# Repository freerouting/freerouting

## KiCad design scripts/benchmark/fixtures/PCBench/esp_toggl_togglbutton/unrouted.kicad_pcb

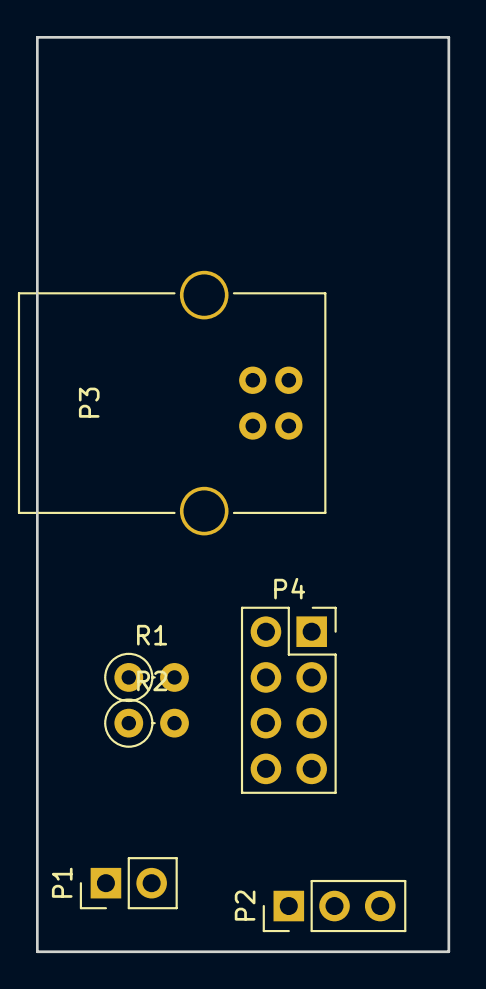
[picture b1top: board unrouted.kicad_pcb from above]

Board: 2 copper layers, 22.9 x 50.8 mm, 7 parts (1 on the bottom side), 7 nets, no tracks yet.

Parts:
P1: Button; Pin_Header_Straight_1x02_Pitch2.54mm
P2: WS2812B; Pin_Header_Straight_1x03_Pitch2.54mm
P3: USB_B
P4: CONN_02X04; Socket_Strip_Straight_2x04_Pitch2.54mm
R1, R2: 10k; R_Axial_DIN0207_L6.3mm_D2.5mm_P2.54mm_Vertical
U1: NCP1117ST33T3G; SOT-223

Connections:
+5V: P2.3, P3.1, U1.3
GND: P1.1, P2.1, P3.4, P3.5, P4.1, U1.1
unnamed: P1.2, P4.5
unnamed: P2.2, P4.3
unnamed: P4.4, R1.2
unnamed: P4.6, R2.2
unnamed: P4.8, R1.1, R2.1, U1.2

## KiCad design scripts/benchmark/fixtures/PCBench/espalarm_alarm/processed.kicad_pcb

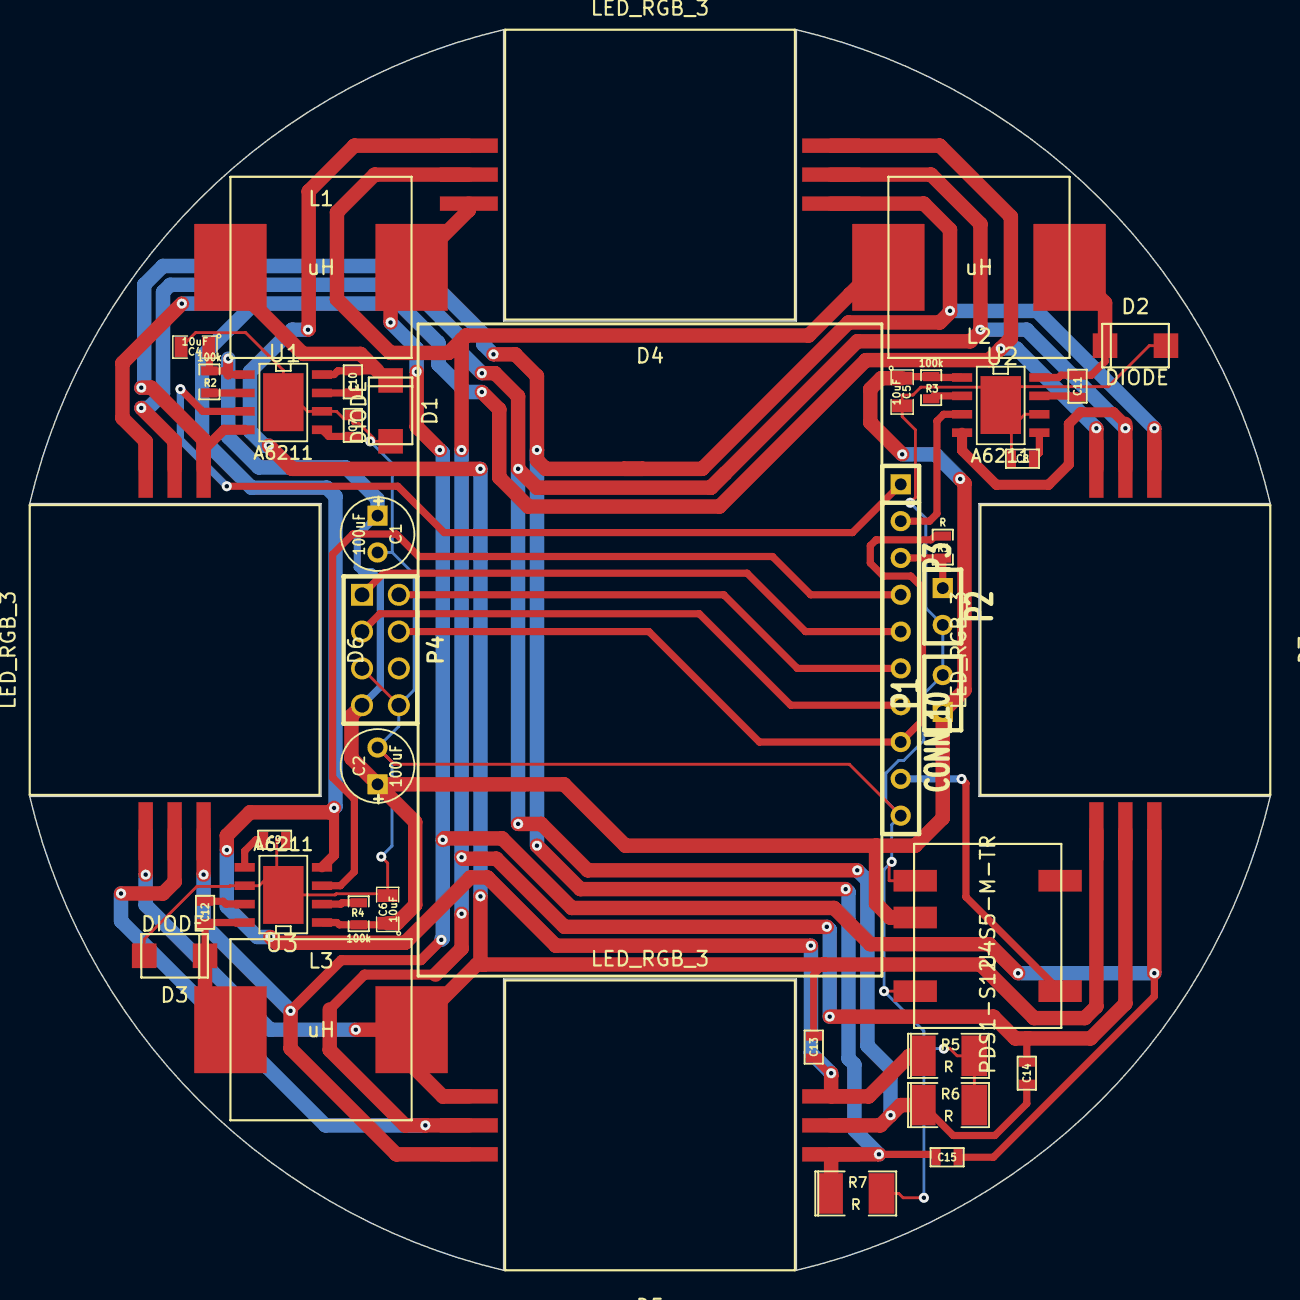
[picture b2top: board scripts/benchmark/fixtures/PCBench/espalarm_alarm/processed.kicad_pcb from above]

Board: 2 copper layers, 85.6 x 85.6 mm, 39 parts (0 on the bottom side), 29 nets.

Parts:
C1, C2: 100uF; C1V5
C4, C5, C6: 10uF; SM0805
C7, C8, C9, C10, C11, C12: 100nF; SM0603
C13, C14, C15: 1uF; SM0603
D1, D2, D3: DIODE; DIODE_SMA
D4, D5, D6, D7: LED_RGB_3; RGB_LED_10W
L1, L2, L3: uH; IND_12.5x12.5mm
P1, P2: CONN_2; SIL-2
P3: CONN_10; SIL-10
P4: CONN_8; pin_array_4x2
R1: R; SM0603_Resistor
R2, R3, R4: 100k; SM0603_Resistor
R5, R6, R7: R; SM1210L
U1, U2, U3: A6211; SO8_WITH_EP
U4: PDS1-S12-S5-M-TR

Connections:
/3.3V: P3.8, P4.4, R1.1
/5V: P3.9, U4.5
/12V: C1.1, C2.1, C4.1, C5.1, C6.1, P1.1, P4.7, R2.1, R3.1, R4.1, U1.1, U2.1, U3.1, U4.2
/GPIO0: P3.7, P4.3
/GPIO2: P3.6, P4.2
/GPIO12: P3.2, U2.3
/GPIO13: P3.4, U3.3
/GPIO14: P3.1, U1.3
/GPIO15: P3.5, P4.1
/GPIO16: P2.1, P3.3, R1.2
GND: C1.2, C2.2, C4.2, C5.2, C6.2, C7.2, C8.2, C9.2, D1.1, D2.1, D3.1, P1.2, P2.2, P3.10, P4.5, P4.8, R5.2, R6.2, R7.2, U1.6, U1.9, U2.6, U2.9, U3.6, U3.9, U4.1, U4.4
unnamed: C14.2, D4.5, D5.5, D6.5, D7.5, R6.1, U2.4
unnamed: C11.1, U2.7
unnamed: C11.2, D2.2, L2.1, U2.8
unnamed: R3.2, U2.2
unnamed: C9.1, U3.5
unnamed: R4.2, U3.2
unnamed: C8.1, U2.5
unnamed: C10.1, U1.7
unnamed: C10.2, D1.2, L1.1, U1.8
unnamed: C12.1, U3.7
unnamed: C12.2, D3.2, L3.1, U3.8
unnamed: C13.1, D4.1, D5.1, D6.1, D7.1, L3.2
unnamed: C7.1, U1.5
unnamed: C15.1, D4.3, D5.3, D6.3, D7.3, L1.2
unnamed: R2.2, U1.2
unnamed: C15.2, D4.4, D5.4, D6.4, D7.4, R7.1, U1.4
unnamed: C13.2, D4.6, D5.6, D6.6, D7.6, R5.1, U3.4
unnamed: C14.1, D4.2, D5.2, D6.2, D7.2, L2.2

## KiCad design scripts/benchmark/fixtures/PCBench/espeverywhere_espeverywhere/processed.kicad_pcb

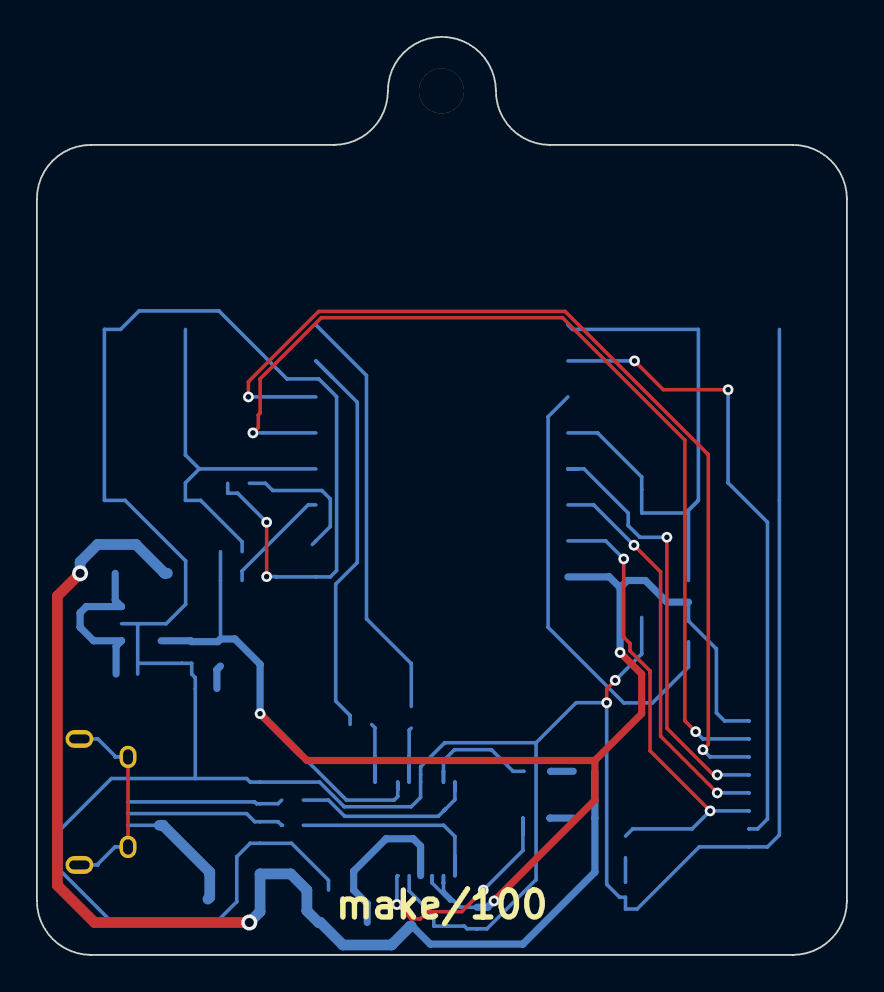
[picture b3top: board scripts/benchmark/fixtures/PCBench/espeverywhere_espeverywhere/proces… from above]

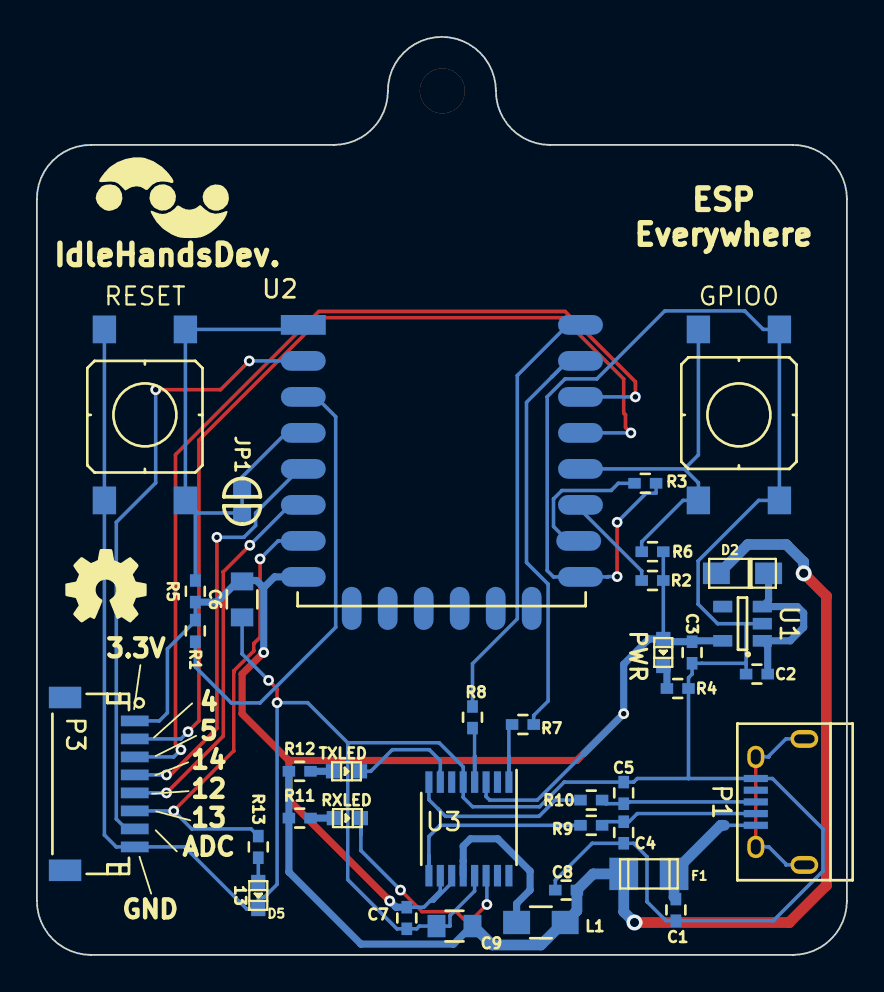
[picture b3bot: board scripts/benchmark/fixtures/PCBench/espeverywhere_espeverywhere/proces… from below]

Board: 2 copper layers, 45.0 x 51.0 mm, 37 parts (37 on the bottom side), 31 nets.

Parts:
C1, C7, C8: 0.1uF; C_0402_Hand
C2: 1uF; C_0402_Hand
C3: 2.2uF; C_0402_Hand
C4, C5: 47pF; C_0402_Hand
C6, C9: 10uF; C_0805
D1: PWR; Led_0603
D2: BAT20J; bat20j
D3: RXLED; Led_0603
D4: TXLED; Led_0603
D5: 13; Led_0603
F1: 500mA; c_1206
JP1: Jumper_NC_Small; SOLDER-JUMPER_1-WAY-CLOSED
L1: FB; R_0805_HandSoldering
P1: USB_OTG; USB_Micro-B
P3: CONN_01X08; Connectors_JST_SM08B-SRSS-TB
R1, R2, R5: 10K; R_0402_Hand
R3, R4, R6, R7, R8, R11, R12, R13: 1K; R_0402_Hand
R9, R10: 27R; R_0402_Hand
SW2: GPIO0; Button_CKN9112CT-ND
SW3: RESET; Button_CKN9112CT-ND
U1: AP2112K-3.3V; SOT-23-5
U2: ESP-12E; ESP-12E_SMD
U3: FT230XS; SSOP-16_3.9x4.9mm_Pitch0.635mm

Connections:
+3V3: C3.1, C6.2, C7.2, D1.2, P3.1, R1.1, R2.1, R5.1, R6.1, U1.5, U2.8, U3.3, U3.10, U3.11
/ADC: P3.7, U2.2
/CH_PD: R1.2, U2.3
/GPIO0: R6.2, SW2.2, U2.18
/GPIO2: R2.2, U2.17
/GPIO4: P3.2, U2.19
/GPIO5: P3.3, U2.20
/GPIO12: P3.5, U2.6
/GPIO13: P3.6, R13.1, U2.7
/GPIO14: P3.4, U2.5
/GPIO15: R3.1, U2.16
/GPIO16: JP1.1, JP1.2, R5.2, SW3.2, U2.1, U2.4
/RXESP: R7.1, U2.21
/TXESP: R8.1, U2.22
GND: C1.1, C2.2, C3.2, C4.1, C5.1, C6.1, C7.1, C8.1, C9.1, D5.1, P1.5, P3.8, R3.2, R4.2, SW2.1, SW3.1, U1.2, U2.15, U3.5, U3.13
unnamed: C1.2, F1.2, P1.1
unnamed: C2.1, D2.1, U1.1, U1.3
unnamed: C4.2, P1.2, R9.2
unnamed: C5.2, P1.3, R10.2
unnamed: D1.1, R4.1
unnamed: D3.1, U3.14
unnamed: D3.2, R11.2
unnamed: D4.1, U3.7
unnamed: D4.2, R12.2
unnamed: D5.2, R13.2
unnamed: L1.1, U3.12
unnamed: R7.2, U3.1
unnamed: R8.2, U3.4
unnamed: R9.1, U3.9
unnamed: R10.1, U3.8
VUSB: C8.2, C9.2, D2.2, F1.1, L1.2, R11.1, R12.1

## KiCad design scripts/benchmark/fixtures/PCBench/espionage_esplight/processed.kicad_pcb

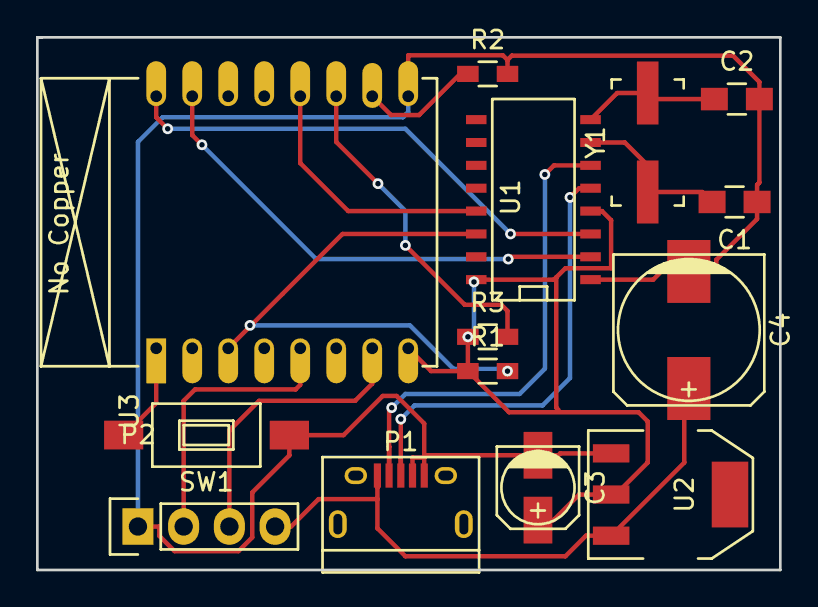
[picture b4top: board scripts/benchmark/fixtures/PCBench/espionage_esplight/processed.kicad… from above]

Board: 2 copper layers, 41.3 x 29.6 mm, 14 parts (0 on the bottom side), 16 nets.

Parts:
C1, C2: 22pF; C_0805_HandSoldering
C3: 22uF; c_elec_4x5.8
C4: 470uF; c_elec_8x10
P1: USB_B; USB_Micro-B
P2: CONN_01X04; Socket_Strip_Straight_1x04
R1, R2, R3: 10kE; R_0603_HandSoldering
SW1: SW_PUSH; SW_SPST_FSMSM
U1: CH340G; SO-16-N
U2: AMS1117; SOT-223
U3: ESP-07v2
Y1: 20MHz; Crystal_CSM-3X_SMD

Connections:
/3.3V: C3.1, R1.1, R3.1, U1.4, U1.16, U2.2, U3.8
/5V: C4.1, P1.1, P2.4, U2.3
/CLOCK: P2.2, U3.5
/DTR: U1.13, U3.12
/GND: C1.1, C2.2, C3.2, C4.2, P1.4, P1.5, P2.1, R2.2, SW1.1, U1.1, U2.1, U3.9
/MOSI: P2.3, U3.7
/RESET: SW1.2, U3.1
/RTS: R1.2, U1.14, U3.3
/RX: U1.3, U3.16
/TX: U1.2, U3.15
unnamed: C1.2, U1.7, Y1.1
unnamed: C2.1, U1.8, Y1.2
unnamed: P1.2, U1.6
unnamed: P1.3, U1.5
unnamed: R2.1, U3.10
unnamed: R3.2, U3.11
